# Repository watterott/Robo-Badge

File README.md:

# Robo-Badge
Learn to Solder Badge based on an Atmel/Microchip ATtiny841 Microcontroller with Micronucleus USB Bootloader. The board is compatible with the Arduino IDE.

* [Microchip ATtiny841](https://www.microchip.com/wwwproducts/en/ATTINY841) @ 8 MHz (internal clock)
* [Micronucleus](https://github.com/micronucleus/micronucleus) USB Bootloader (Arduino compatible)
* IR-LEDs to [send infrared codes](https://github.com/watterott/Robo-Badge/tree/master/software/TV-Off) (e.g. TV-B-Gone)
* LEDs, Buttons, Pin Connectors...
* MicroUSB connector for programming/communication
* Power Supply: CR2032 (3V) / LIR2032 (3.6V) cell battery or USB
* Open-Source and released under the [Creative Commons Attribution Share-Alike License](https://creativecommons.org/licenses/by-sa/4.0/).
* **[Documentation on learn.watterott.com](https://learn.watterott.com)**

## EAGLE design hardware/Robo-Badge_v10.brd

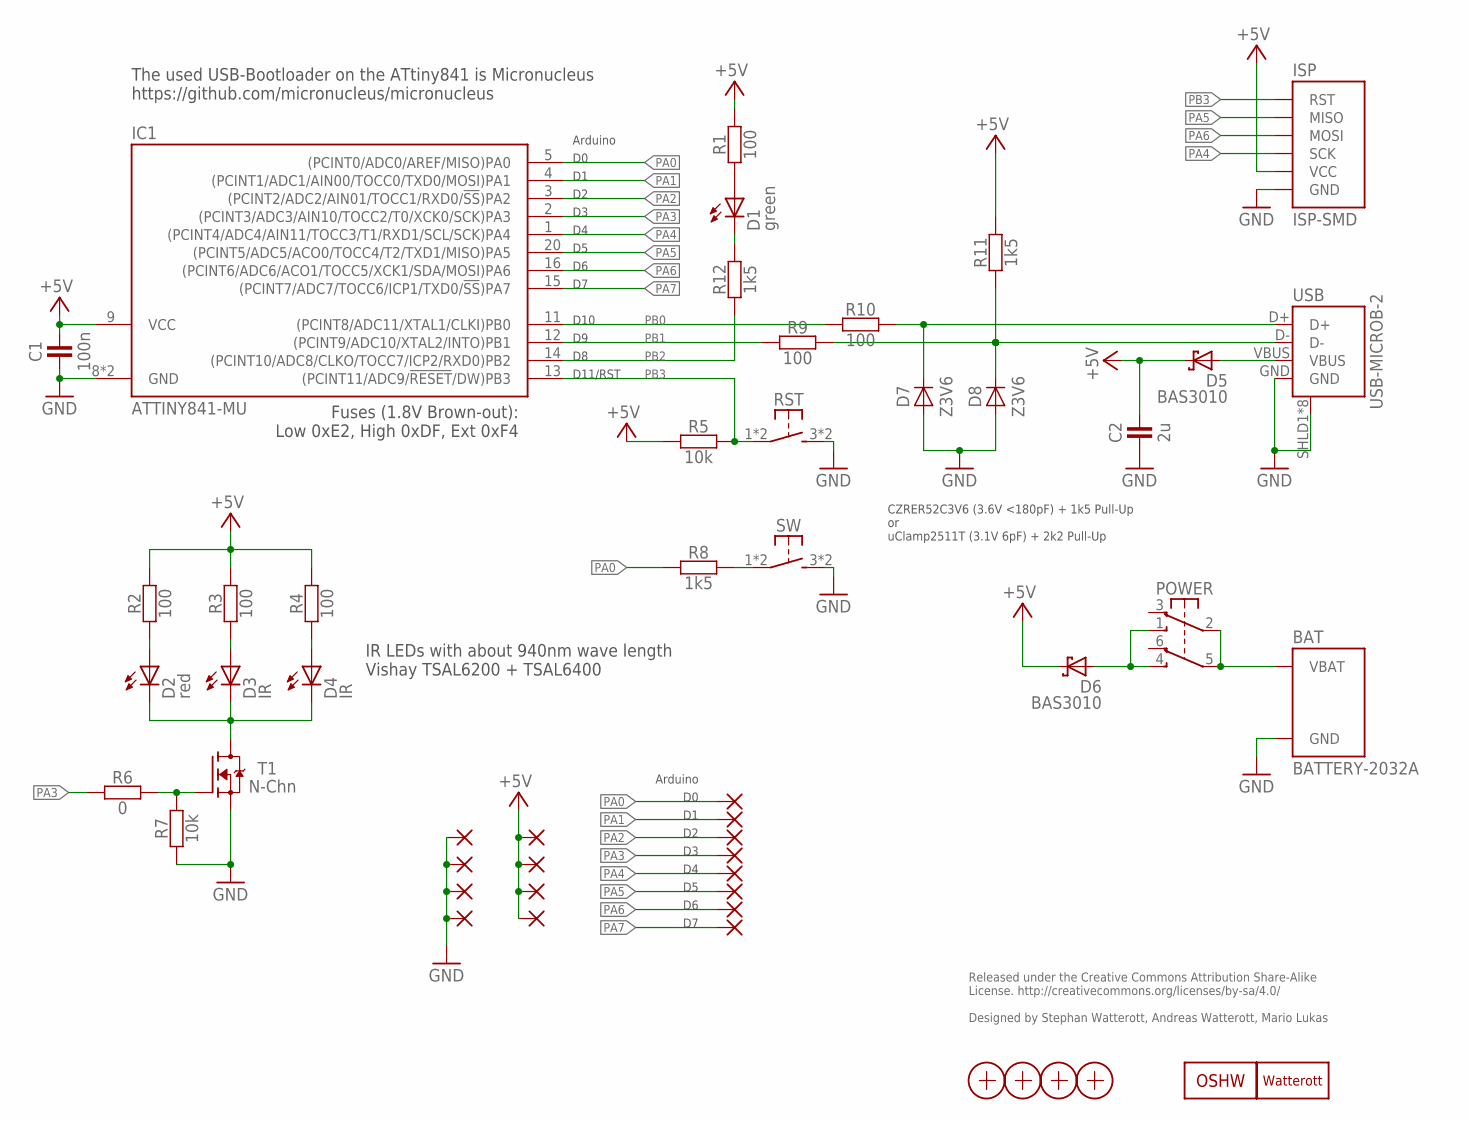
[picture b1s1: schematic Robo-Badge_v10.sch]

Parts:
BAT: BATTERY-2032A; BAT-4UC-05581
C1: 100n; C0402
C2: 2u; C0402
D1: green; LED_5MM
D2: red; LED_5MM
D3, D4: IR; LED_5MM
D5, D6: BAS3010; SOD323
D7, D8: Z3V6; SOD723
GND_1, GND_2, GND_3, GND_4: PAD-WEARABLE
IC1: ATTINY841-MU; QFN20-PAD
ISP: ISP-SMD; ISP-2X3_SMD
LOGO1: LOGO-S_PLACE_M; SPARK_TPLACE_M
LOGO2: OSHW_LOGOX0150; OSHW_6X150
PA0, PA1, PA2, PA3, PA4, PA5, PA6, PA7: PAD-WEARABLE
POWER: SW-2UM-CUS22B; CUS22B
R1, R2, R3, R4: 100; R0207/10-LARGE_PADS
R5, R7: 10k; C0402
R6: 0; C0402
R8, R11, R12: 1k5; C0402
R9, R10: 100; C0402
RST: SW-TACTILE-6X6; SW6X6
SW: SW-TACTILE-6X6; SW6X6
T1: N-Chn; SOT23
USB: USB-MICROB-2; USB-MICROB-10118194
VCC_1, VCC_2, VCC_3, VCC_4: PAD-WEARABLE
X1, X2, X3, X4: PASSER-07; PASSER_07MM

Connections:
+5V: C1.2, C2.2, D5.C, D6.C, IC1.9 (VCC), ISP.VCC, R1.2, R2.1, R3.1, R4.1, R5.2, R11.1, VCC_1.1, VCC_1.2, VCC_1.3, VCC_2.1, VCC_2.2, VCC_2.3, VCC_3.1, VCC_3.2, VCC_3.3, VCC_4.1, VCC_4.2, VCC_4.3
DC: D2.C, D3.C, D4.C, T1.3 (D)
D_N: D8.C, R9.2, R11.2, USB.D-
D_P: D7.C, R10.2, USB.D+
GND: BAT.GND, C1.1, C2.1, D7.A, D8.A, GND_1.1, GND_1.2, GND_1.3, GND_2.1, GND_2.2, GND_2.3, GND_3.1, GND_3.2, GND_3.3, GND_4.1, GND_4.2, GND_4.3, IC1.8 (GND), IC1.TP (GND), ISP.GND, R7.2, RST.3 (S1), RST.4 (S1), SW.3 (S1), SW.4 (S1), T1.2 (S), USB.GND, USB.SHLD1 (SHIELD), USB.SHLD2 (SHIELD), USB.SHLD3 (SHIELD), USB.SHLD4 (SHIELD), USB.SHLD5 (SHIELD), USB.SHLD6 (SHIELD), USB.SHLD7 (SHIELD), USB.SHLD8 (SHIELD)
LED: R6.1, R7.1, T1.1 (G)
LED+: D1.A, R1.1
LED-: D1.C, R12.1
PA0: IC1.5 ((PCINT0/ADC0/AREF/MISO)PA0), PA0.1, PA0.2, PA0.3, R8.1
PA1: IC1.4 ((PCINT1/ADC1/AIN00/TOCC0/TXD0/MOSI)PA1), PA1.1, PA1.2, PA1.3
PA2: IC1.3 ((PCINT2/ADC2/AIN01/TOCC1/RXD0/!SS!)PA2), PA2.1, PA2.2, PA2.3
PA3: IC1.2 ((PCINT3/ADC3/AIN10/TOCC2/T0/XCK0/SCK)PA3), PA3.1, PA3.2, PA3.3, R6.2
PA4: IC1.1 ((PCINT4/ADC4/AIN11/TOCC3/T1/RXD1/SCL/SC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), ISP.SCK, PA4.1, PA4.2, PA4.3
PA5: IC1.20 ((PCINT5/ADC5/ACO0/TOCC4/T2/TXD1/MISO)PA5), ISP.MISO, PA5.1, PA5.2, PA5.3
PA6: IC1.16 ((PCINT6/ADC6/ACO1/TOCC5/XCK1/SDA/MOSI)P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), ISP.MOSI, PA6.1, PA6.2, PA6.3
PA7: IC1.15 ((PCINT7/ADC7/TOCC6/ICP1/TXD0/!SS!)PA7), PA7.1, PA7.2, PA7.3
PB0: IC1.11 ((PCINT8/ADC11/XTAL1/CLKI)PB0), R10.1
PB1: IC1.12 ((PCINT9/ADC10/XTAL2/INTO)PB1), R9.1
PB2: IC1.14 ((PCINT10/ADC8/CLKO/TOCC7/ICP2/RXD0)PB2), R12.2
PB3: IC1.13 ((PCINT11/ADC9/!RESET!/DW)PB3), ISP.RST, R5.1, RST.1, RST.2 (P1)
RD2: D2.A, R2.2
RD3: D3.A, R3.2
RD4: D4.A, R4.2
SW: R8.2, SW.1, SW.2 (P1)
VBAT: BAT.VBAT, POWER.2 (P1), POWER.5 (P2)
VBUS: D5.A, USB.VBUS
VCC: D6.A, POWER.1 (S1), POWER.4 (S2)

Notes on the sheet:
The used USB-Bootloader on the ATtiny841 is Micronucleus https://github.com/micronucleus/micronucleus
CZRER52C3V6 (3.6V <180pF) + 1k5 Pull-Up or uClamp2511T (3.1V 6pF) + 2k2 Pull-Up
Arduino
D10
D11/RST
IR LEDs with about 940nm wave length Vishay TSAL6200 + TSAL6400
Fuses (1.8V Brown-out): Low 0xE2, High 0xDF, Ext 0xF4
Released under the Creative Commons Attribution Share-Alike License. http://creativecommons.org/licenses/by-sa/4.0/ Designed by Stephan Watterott, Andreas Watterott, Mario Lukas

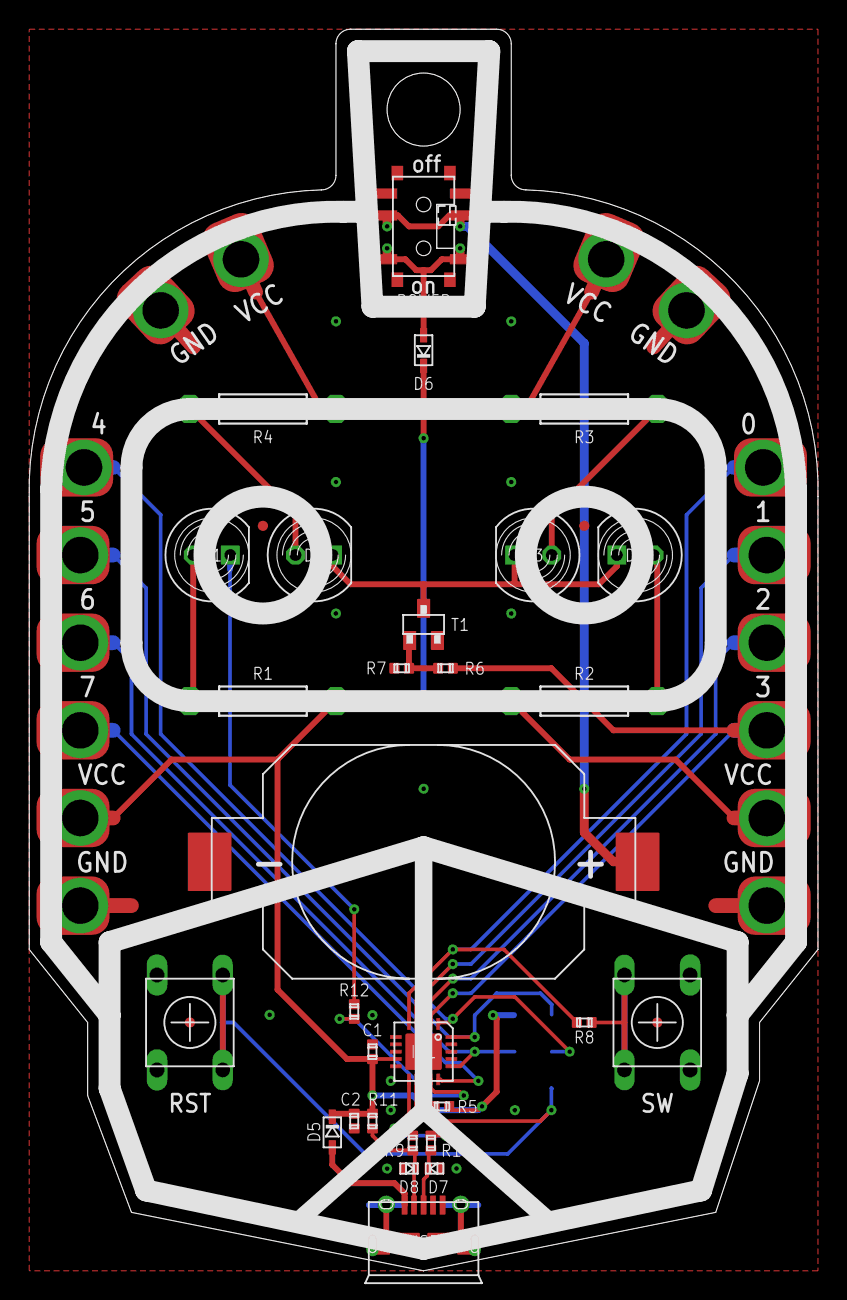
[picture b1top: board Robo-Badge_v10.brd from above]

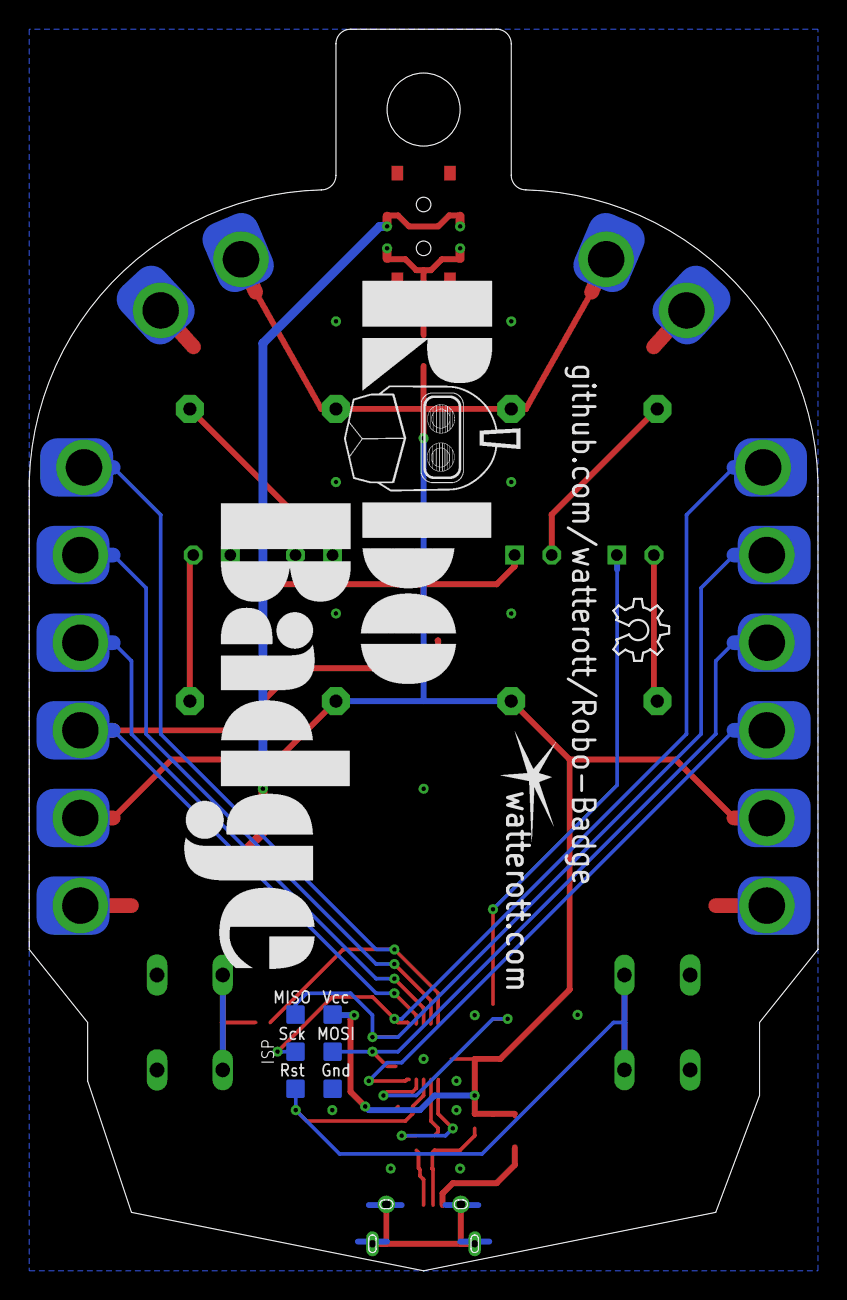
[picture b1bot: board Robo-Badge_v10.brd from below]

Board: 2 copper layers, 54.0 x 85.0 mm, 52 parts (3 on the bottom side), 27 nets.

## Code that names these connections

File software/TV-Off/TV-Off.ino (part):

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  other parts of the world that use PAL video).

  Hardware:
  PA3/D3 (OC0B/TOCC2) - IR-LED
  PB2/D8 - Normal LED
  PA0/D0 - Trigger Switch (SW)
  PA4/D4 - Optional Region Switch

  Board: ATtiny841 (8MHz)
  Core:  Standard Arduino (pin map from David A. Mellis)
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
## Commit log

2017-09-12 updated schematics
2017-10-19 updated comments
2018-01-30 moved files
2020-05-16 updated examples
